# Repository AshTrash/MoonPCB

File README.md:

# MoonPCB
Ashur, Patrick, and Matthew "Floppy Balls" Schettino

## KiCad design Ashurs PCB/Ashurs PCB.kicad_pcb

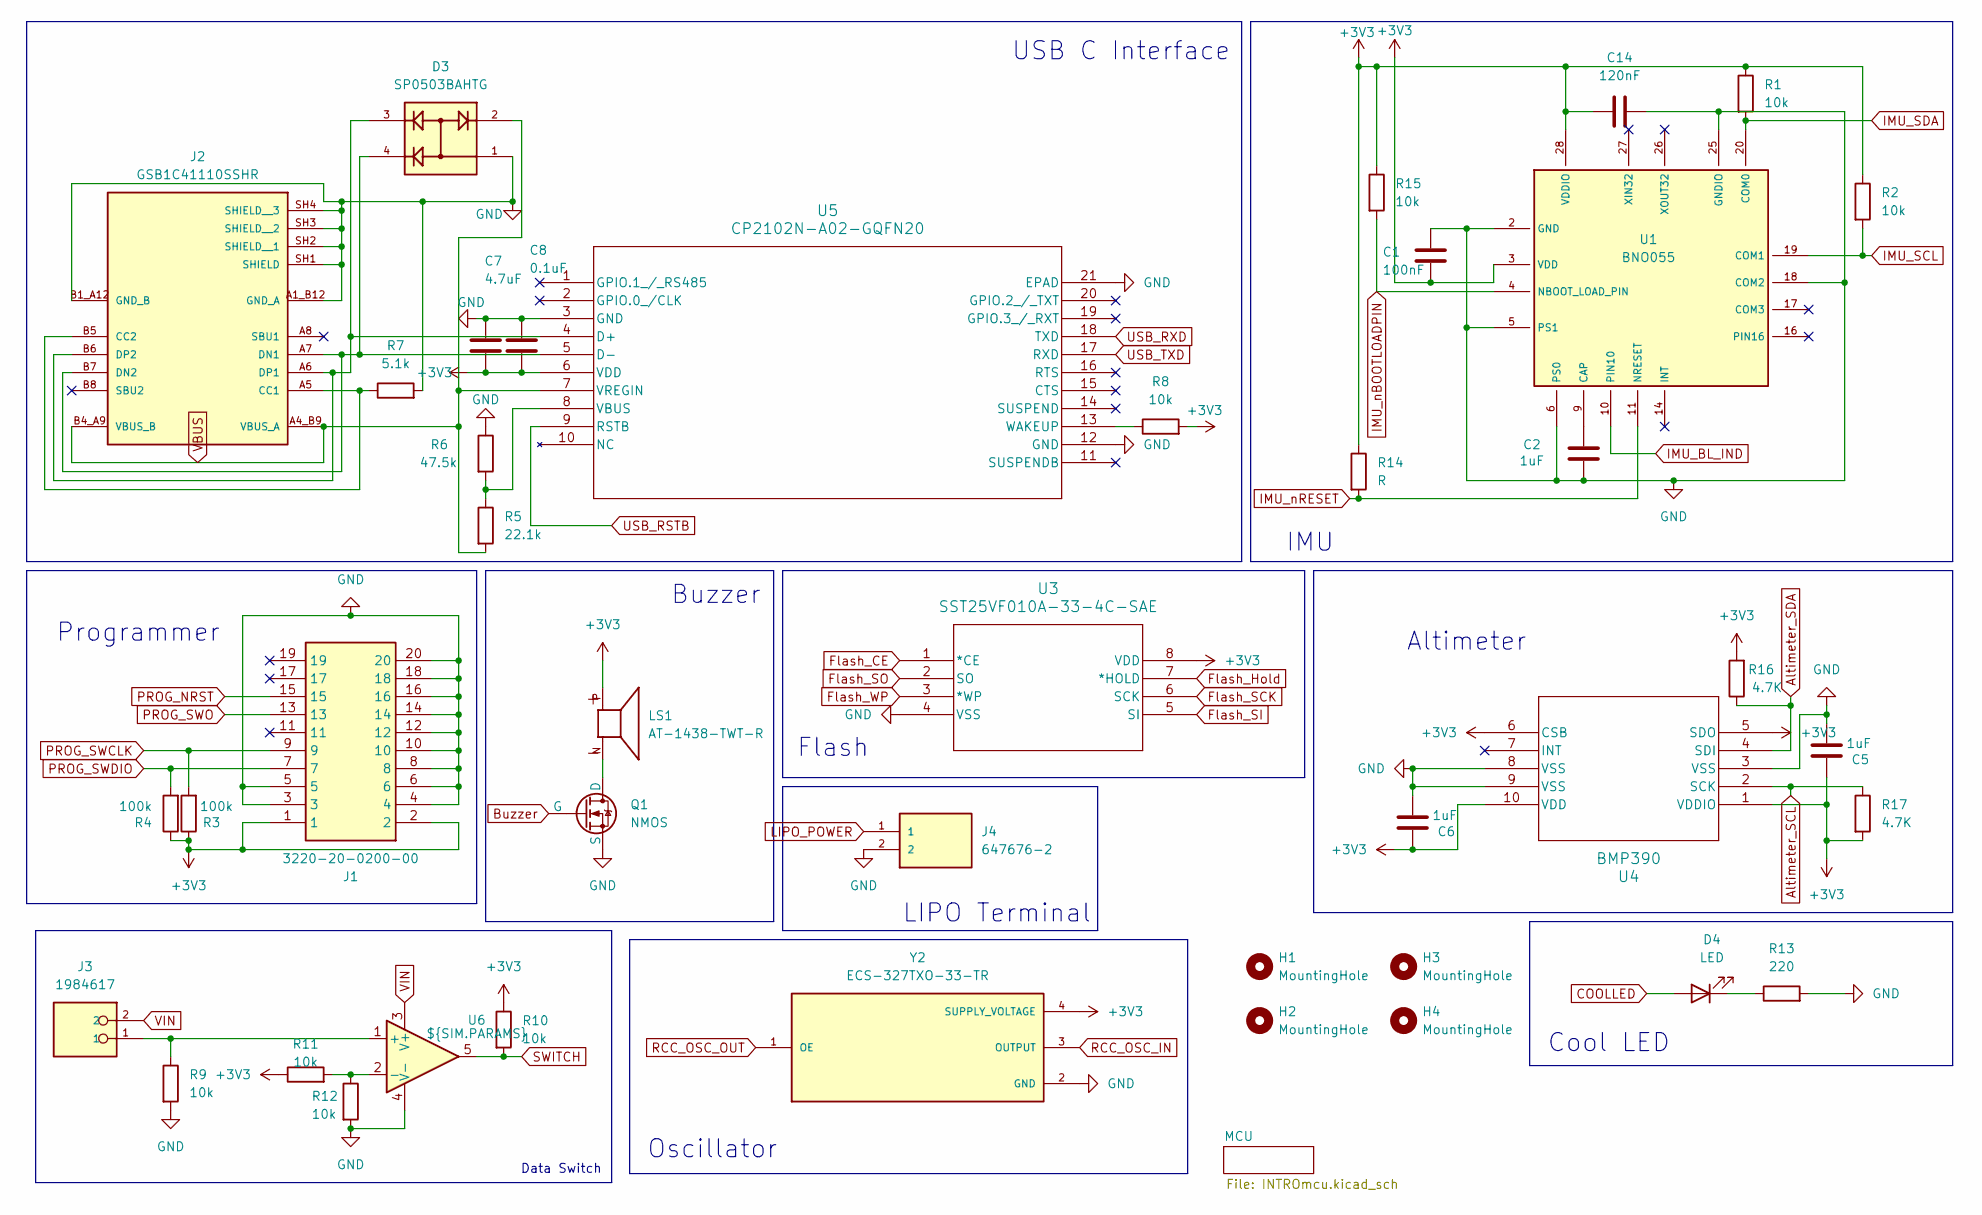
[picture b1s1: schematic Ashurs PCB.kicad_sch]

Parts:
C1: 100nF; C_0603_1608Metric
C2, C5, C6: 1uF; C_0603_1608Metric
C7: 4.7uF; C_0603_1608Metric
C8: 0.1uF; C_0603_1608Metric
C14: 120nF; C_0603_1608Metric
D3: SP0503BAHTG; SOT-143; PARTREV N/A
D4: LED; D_0201_0603Metric
H1, H2, H3, H4: MountingHole; MountingHole_2.2mm_M2
J1: 3220-20-0200-00; 322020020000; Manufacturer_Part_Number 3220-20-0200-00
J2: GSB1C41110SSHR; AMPHENOL_GSB1C41110SSHR; PARTREV AX1
J3: 1984617; PHOENIX_1984617; PARTREV 22.08.2018
J4: 647676-2; TE_647676-2; PARTREV R
LS1: AT-1438-TWT-R; XDCR_AT-1438-TWT-R; PARTREV H
Q1: NMOS; TSOT-23
R1, R2, R8, R9, R10, R11, R12, R15: 10k; R_0603_1608Metric
R3, R4: 100k; R_0603_1608Metric
R5: 22.1k; R_0603_1608Metric
R6: 47.5k; R_0603_1608Metric
R7: 5.1k; R_0603_1608Metric
R13: 220; R_0603_1608Metric
R14: R; R_0603_1608Metric
R16, R17: 4.7K; R_0603_1608Metric
U1: BNO055; LGA28R50P4X10_380X520X100
U3: SST25VF010A-33-4C-SAE; SOIC8_SA_SST_MCH
U4: BMP390; 10LGA_2X2X0p75_BOS
U5: CP2102N-A02-GQFN20; QFN20_CP2102N_SIL
U6: ${SIM.PARAMS}; SOT-23-5
Y2: ECS-327TXO-33-TR; OSC_ECS-327TXO-33-TR; PARTREV Rev.2019

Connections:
+3V3: C1.2, C5.1, C6.1, C7.2, C8.2, C14.1, J1.1, J1.2, LS1.P, R1.1, R2.1, R3.1, R4.1, R8.2, R10.1, R11.1, R14.1, R15.1, R16.2, R17.2, U1.3 (VDD), U1.28 (VDDIO), U3.8 (VDD), U4.1 (VDDIO), U4.5 (SDO), U4.6 (CSB), U4.10 (VDD), U5.6 (VDD), Y2.4 (SUPPLY_VOLTAGE); also elsewhere on the board
Altimeter_SCL: R2.2, R17.1, U1.19 (COM1), U4.2 (SCK); also elsewhere on the board
Altimeter_SDA: R1.2, R16.1, U1.20 (COM0), U4.4 (SDI); also elsewhere on the board
Buzzer: Q1.2 (G); also elsewhere on the board
COOLLED: D4.2 (A); also elsewhere on the board
Flash_CE: U3.1 (*CE); also elsewhere on the board
Flash_Hold: U3.7 (*HOLD); also elsewhere on the board
Flash_SCK: U3.6 (SCK); also elsewhere on the board
Flash_SI: U3.5 (SI); also elsewhere on the board
Flash_SO: U3.2 (SO); also elsewhere on the board
Flash_WP: U3.3 (*WP); also elsewhere on the board
GND: C1.1, C2.2, C5.2, C6.2, C7.1, C8.1, C14.2, D3.1, J1.3, J1.4, J1.5, J1.6, J1.8, J1.10, J1.12, J1.14, J1.16, J1.18, J1.20, J2.A1_B12 (GND_A), J2.B1_A12 (GND_B), J2.SH1 (SHIELD), J2.SH2 (SHIELD__1), J2.SH3 (SHIELD__2), J2.SH4 (SHIELD__3), J4.2, Q1.3 (S), R6.1, R7.2, R9.2, R12.2, R13.2, U1.2 (GND), U1.5 (PS1), U1.6 (PS0), U1.18 (COM2), U1.25 (GNDIO), U3.4 (VSS), U4.3 (VSS), U4.8 (VSS), U4.9 (VSS), U5.3 (GND), U5.12 (GND), U5.21 (EPAD), U6.4 (V-), Y2.2 (GND); also elsewhere on the board
IMU_BL_IND: U1.10 (PIN10); also elsewhere on the board
IMU_nBOOTLOADPIN: R15.2, U1.4 (NBOOT_LOAD_PIN); also elsewhere on the board
IMU_nRESET: R14.2, U1.11 (NRESET); also elsewhere on the board
LIPO_POWER: J4.1; also elsewhere on the board
NRST: J1.15; also elsewhere on the board
unnamed: D4.1 (K), R13.1
unnamed: J2.A5 (CC1), J2.B5 (CC2), R7.1
unnamed: D3.4, J2.A7 (DN1), J2.B7 (DN2), U5.5 (D-)
unnamed: D3.3, J2.A6 (DP1), J2.B6 (DP2), U5.4 (D+)
unnamed: LS1.N, Q1.1 (D)
unnamed: C2.1, U1.9 (CAP)
unnamed: R5.1, R6.2, U5.8 (VBUS)
unnamed: R8.1, U5.13 (WAKEUP)
unnamed: J3.1, R9.1, U6.1 (+)
unnamed: R11.2, R12.1, U6.2 (-)
PROG_SWCLK: J1.9, R3.2; also elsewhere on the board
PROG_SWDIO: J1.7, R4.2; also elsewhere on the board
PROG_SWO: J1.13; also elsewhere on the board
RCC_OSC_IN: Y2.3 (OUTPUT); also elsewhere on the board
RCC_OSC_OUT: Y2.1 (OE); also elsewhere on the board
SWITCH: R10.2, U6.5; also elsewhere on the board
USB_RSTB: U5.9 (RSTB); also elsewhere on the board
USB_RXD: U5.18 (TXD); also elsewhere on the board
USB_TXD: U5.17 (RXD); also elsewhere on the board
VBUS: D3.2, J2.A4_B9 (VBUS_A), J2.B4_A9 (VBUS_B), R5.2, U5.7 (VREGIN); also elsewhere on the board
VIN: J3.2, U6.3 (V+); also elsewhere on the board

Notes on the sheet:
Cool LED
IMU
Programmer
Buzzer
USB C Interface
Flash
Oscillator
Data Switch
LIPO Terminal
Altimeter

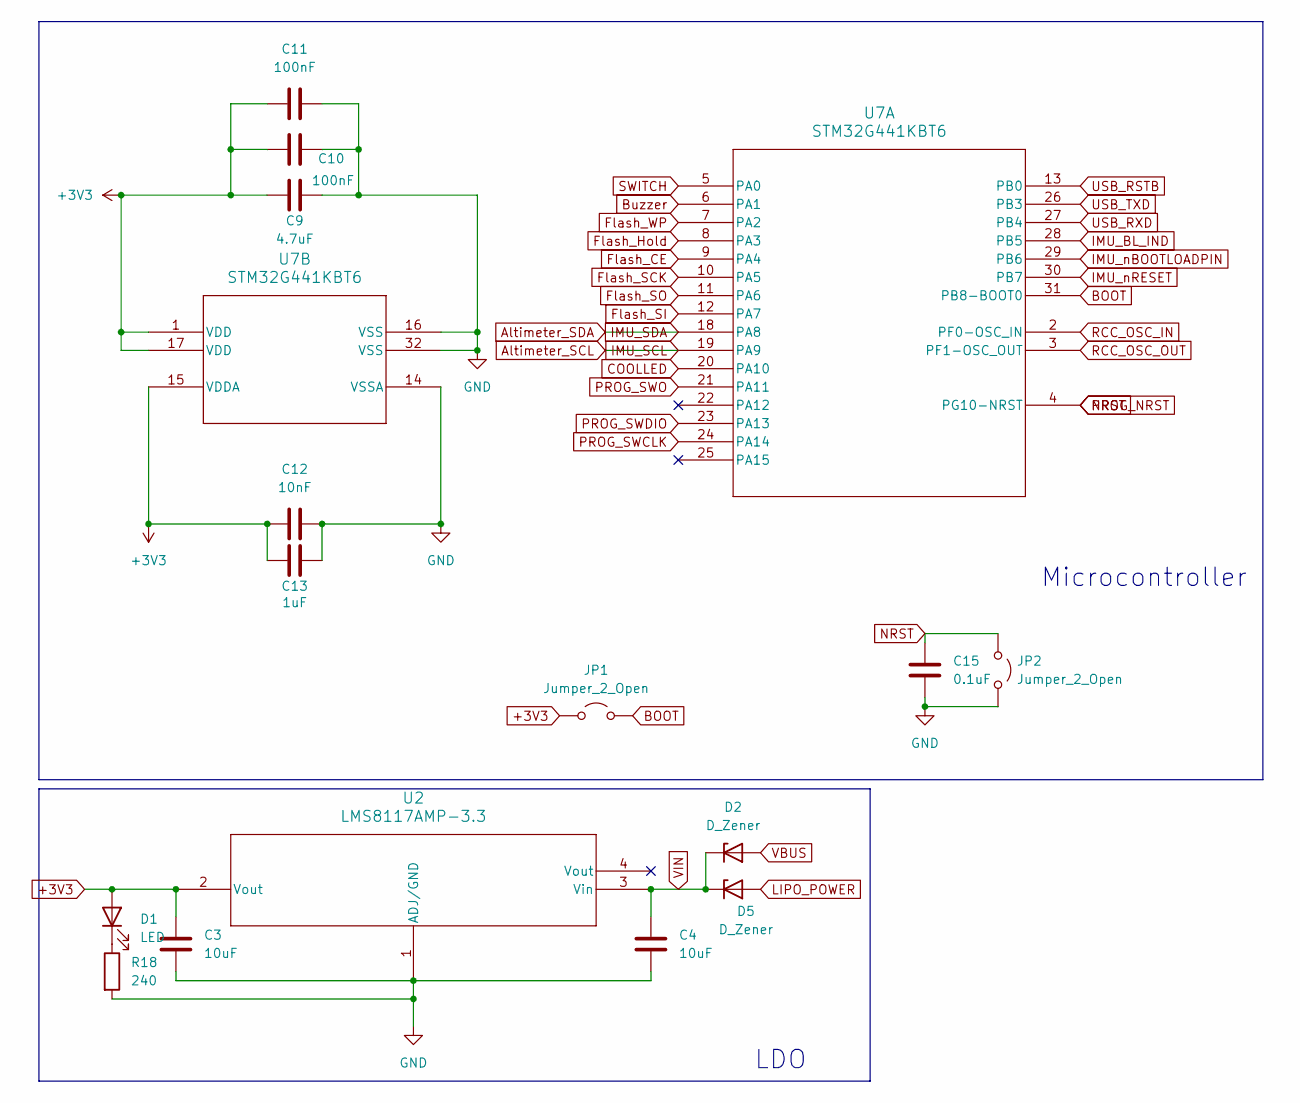
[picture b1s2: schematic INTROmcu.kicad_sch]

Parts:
C3, C4: 10uF; C_0603_1608Metric
C9: 4.7uF; C_0603_1608Metric
C10, C11: 100nF; C_0603_1608Metric
C12: 10nF; C_0603_1608Metric
C13: 1uF; C_0603_1608Metric
C15: 0.1uF; C_0201_0603Metric
D1: LED; LED_0603_1608Metric
D2, D5: D_Zener; D_SOD-123F
JP1, JP2: Jumper_2_Open; R_0201_0603Metric
R18: 240; R_0603_1608Metric
U2: LMS8117AMP-3.3; MP04A_TEX
U7: STM32G441KBT6; LQFP-32

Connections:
+3V3: C3.1, C9.1, C10.1, C11.1, C12.1, C13.1, D1.2 (A), JP1.1 (A), U2.2 (Vout), U7.1 (VDD), U7.15 (VDDA), U7.17 (VDD); also elsewhere on the board
Altimeter_SCL: U7.19 (PA9); also elsewhere on the board
Altimeter_SDA: U7.18 (PA8); also elsewhere on the board
BOOT: JP1.2 (B), U7.31 (PB8-BOOT0)
Buzzer: U7.6 (PA1); also elsewhere on the board
COOLLED: U7.20 (PA10); also elsewhere on the board
Flash_CE: U7.9 (PA4); also elsewhere on the board
Flash_Hold: U7.8 (PA3); also elsewhere on the board
Flash_SCK: U7.10 (PA5); also elsewhere on the board
Flash_SI: U7.12 (PA7); also elsewhere on the board
Flash_SO: U7.11 (PA6); also elsewhere on the board
Flash_WP: U7.7 (PA2); also elsewhere on the board
GND: C3.2, C4.2, C9.2, C10.2, C11.2, C12.2, C13.2, C15.2, JP2.2 (B), R18.2, U2.1 (ADJ/GND), U7.14 (VSSA), U7.16 (VSS), U7.32 (VSS); also elsewhere on the board
IMU_BL_IND: U7.28 (PB5); also elsewhere on the board
IMU_nBOOTLOADPIN: U7.29 (PB6); also elsewhere on the board
IMU_nRESET: U7.30 (PB7); also elsewhere on the board
LIPO_POWER: D5.2 (A); also elsewhere on the board
NRST: C15.1, JP2.1 (A), U7.4 (PG10-NRST); also elsewhere on the board
unnamed: D1.1 (K), R18.1
PROG_SWCLK: U7.24 (PA14); also elsewhere on the board
PROG_SWDIO: U7.23 (PA13); also elsewhere on the board
PROG_SWO: U7.21 (PA11); also elsewhere on the board
RCC_OSC_IN: U7.2 (PF0-OSC_IN); also elsewhere on the board
RCC_OSC_OUT: U7.3 (PF1-OSC_OUT); also elsewhere on the board
SWITCH: U7.5 (PA0); also elsewhere on the board
USB_RSTB: U7.13 (PB0); also elsewhere on the board
USB_RXD: U7.27 (PB4); also elsewhere on the board
USB_TXD: U7.26 (PB3); also elsewhere on the board
VBUS: D2.2 (A); also elsewhere on the board
VIN: C4.1, D2.1 (K), D5.1 (K), U2.3 (Vin); also elsewhere on the board

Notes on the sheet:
Microcontroller
LDO

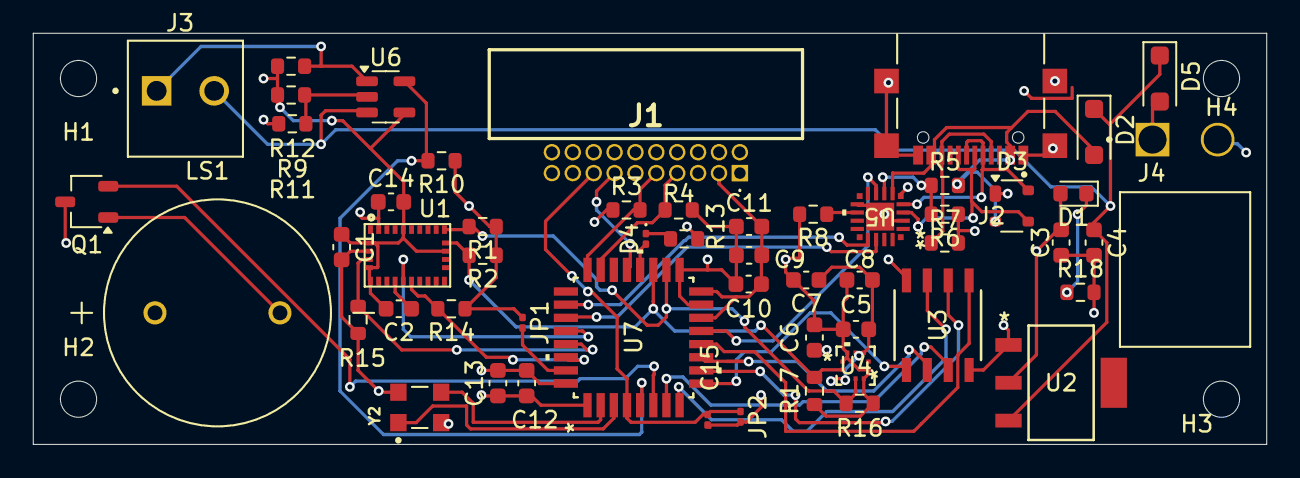
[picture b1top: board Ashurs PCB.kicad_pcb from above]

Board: 4 copper layers, 75.0 x 25.0 mm, 58 parts (0 on the bottom side), 40 nets.

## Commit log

2025-10-18 Beginnings
2026-02-19 PCB check by david push
2026-02-26 post-david suggestions
    u6 footprint, zener diode footprints, jumper footprints
2026-02-27 Gerber and CSV's
2026-03-04 footprint mistake
